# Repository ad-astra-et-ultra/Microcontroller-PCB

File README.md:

# Microcontroller-PCB
A general-purpose microcontroller PCB design for various applications.

## Schematic

## PCB

## 3D View

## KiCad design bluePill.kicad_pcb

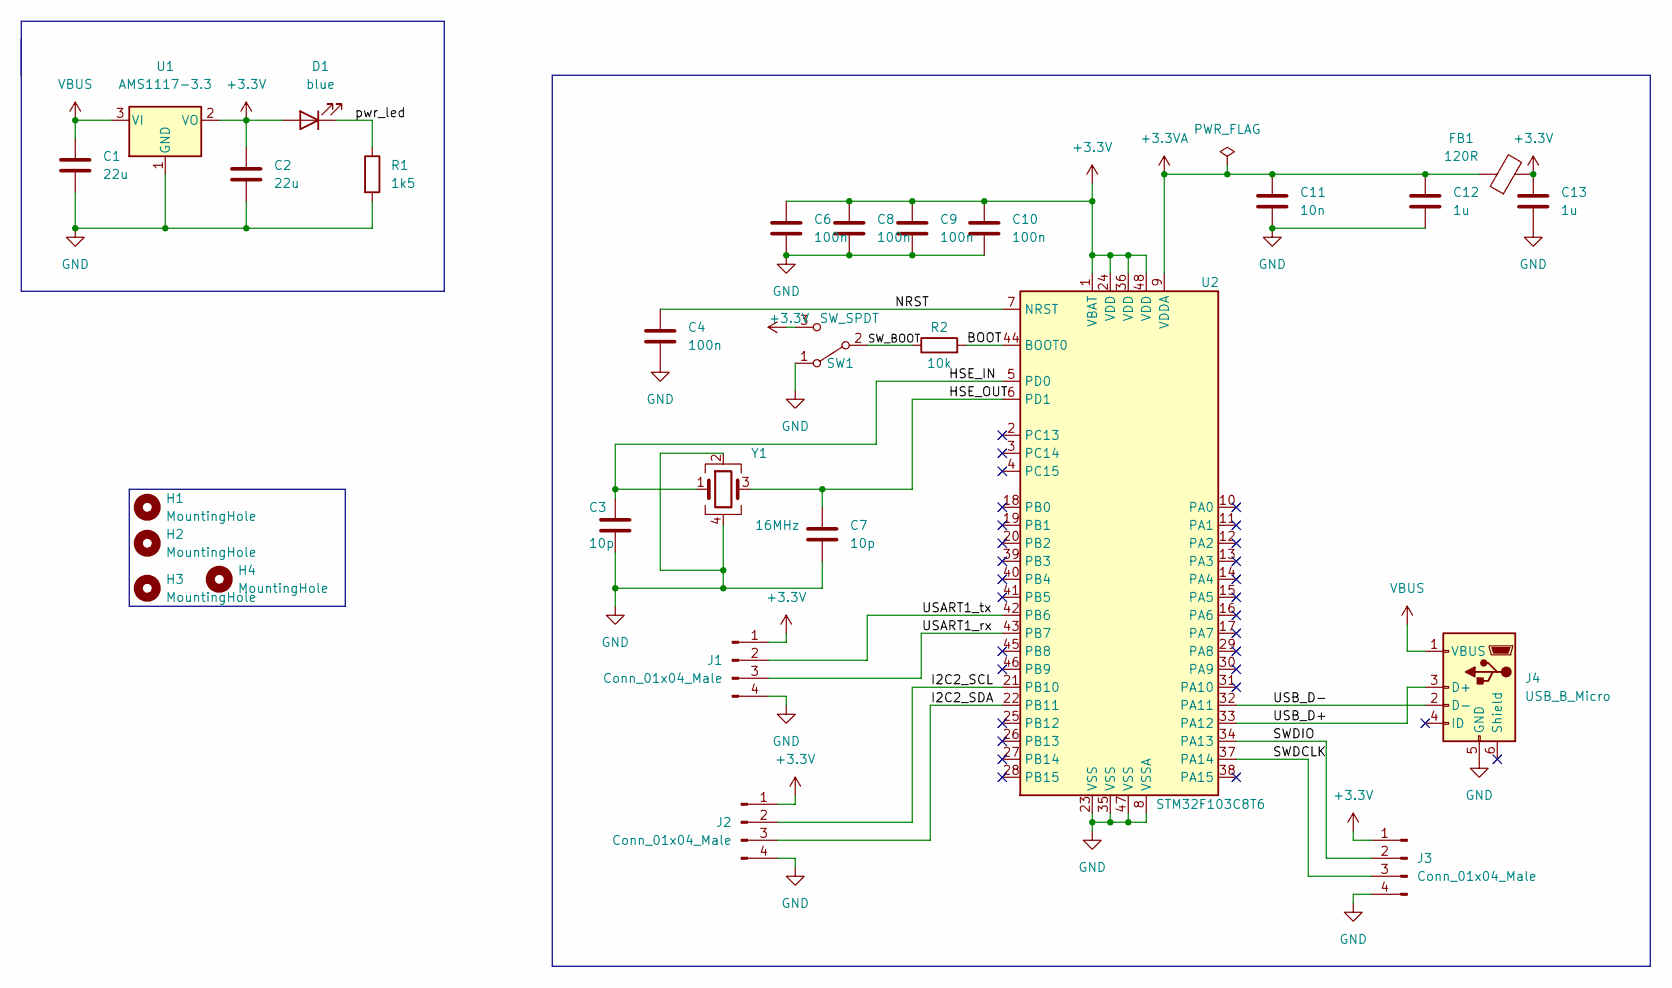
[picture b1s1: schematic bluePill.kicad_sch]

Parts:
C1, C2: 22u; C_0805_2012Metric
C3: 10p; C_0603_1608Metric
C4, C6, C8, C9, C10: 100n; C_0402_1005Metric
C7: 10p; C_0402_1005Metric
C11: 10n; C_0402_1005Metric
C12, C13: 1u; C_0402_1005Metric
D1: blue; LED_0603_1608Metric
FB1: 120R; L_0603_1608Metric
H1, H2, H3, H4: MountingHole; MountingHole_2.2mm_M2
J1, J2, J3: Conn_01x04_Male; PinHeader_1x04_P2.54mm_Vertical
J4: USB_B_Micro; USB_Micro-B_Wuerth_629105150521
R1: 1k5; R_0402_1005Metric
R2: 10k; R_0402_1005Metric
SW1: SW_SPDT; SW_SPDT_PCM12
U1: AMS1117-3.3; SOT-223-3_TabPin2
U2: STM32F103C8T6; LQFP-48_7x7mm_P0.5mm
Y1: 16MHz; Crystal_SMD_3225-4Pin_3.2x2.5mm

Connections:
+3.3VA: C11.1, C12.1, FB1.1, U2.9 (VDDA)
+3V3: C2.1, C6.1, C8.1, C9.1, C10.1, C13.1, D1.2 (A), FB1.2, J1.1, J2.1, J3.1, SW1.3 (C), U1.2 (VO), U2.1 (VBAT), U2.24 (VDD), U2.36 (VDD), U2.48 (VDD)
/BOOT: R2.2, U2.44 (BOOT0)
/HSE_IN: C3.1, U2.5 (PD0), Y1.1
/HSE_OUT: C7.1, U2.6 (PD1), Y1.3
/I2C2_SCL: J2.2, U2.21 (PB10)
/I2C2_SDA: J2.3, U2.22 (PB11)
/NRST: C4.1, U2.7 (NRST)
/SWDCLK: J3.3, U2.37 (PA14)
/SWDIO: J3.2, U2.34 (PA13)
/SW_BOOT: R2.1, SW1.2 (B)
/USART1_rx: J1.3, U2.43 (PB7)
/USART1_tx: J1.2, U2.42 (PB6)
/USB_D+: J4.3 (D+), U2.33 (PA12)
/USB_D-: J4.2 (D-), U2.32 (PA11)
/pwr_led: D1.1 (K), R1.1
GND: C1.2, C2.2, C3.2, C4.2, C6.2, C7.2, C8.2, C9.2, C10.2, C11.2, C12.2, C13.2, J1.4, J2.4, J3.4, J4.5 (GND), R1.2, SW1.1 (A), U1.1 (GND), U2.8 (VSSA), U2.23 (VSS), U2.35 (VSS), U2.47 (VSS), Y1.2, Y1.4
VBUS: C1.1, J4.1 (VBUS), U1.3 (VI)

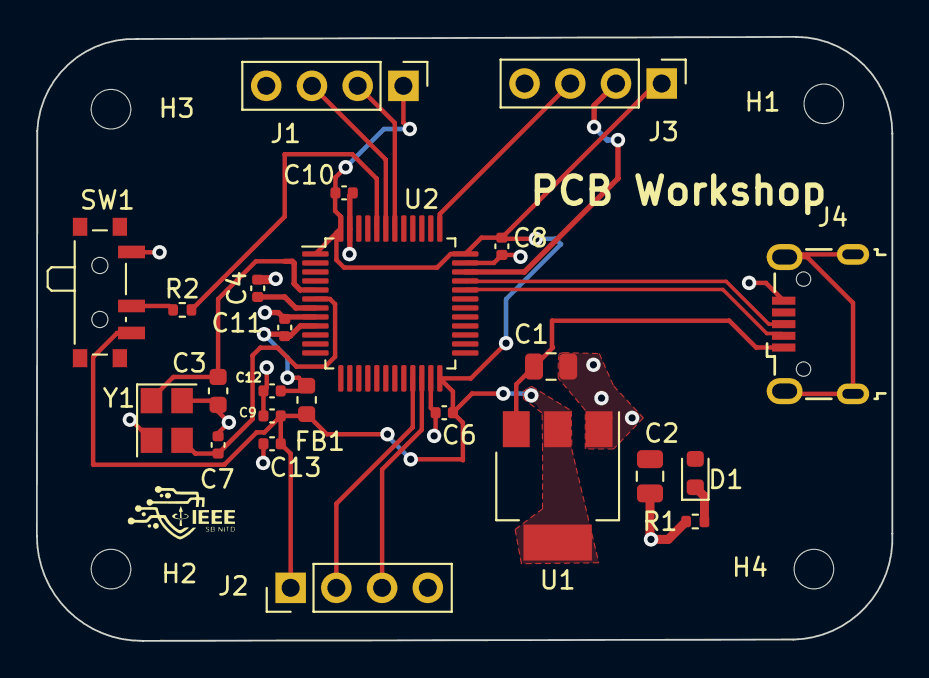
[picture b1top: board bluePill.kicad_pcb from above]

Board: 2 copper layers, 47.5 x 33.6 mm, 29 parts (0 on the bottom side), 18 nets.

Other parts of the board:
PCB Workshop: LOGO
